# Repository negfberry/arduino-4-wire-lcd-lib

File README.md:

# arduino-4-wire-lcd-lib
Arduino 3 or 4 wire LCD library and hardware adapter.
Allows cheap 16x1, 16x2, 20x4 etc. LCDs to connect to an Arduino or similar using only 3 or 4 pins. Supports custom characters, and allows variable contrast (eight levels), and either backlight on/off (3 wire), or variable backlight (256 levels, 4 wire).

Includes library compatible with the Arduino LCD library.

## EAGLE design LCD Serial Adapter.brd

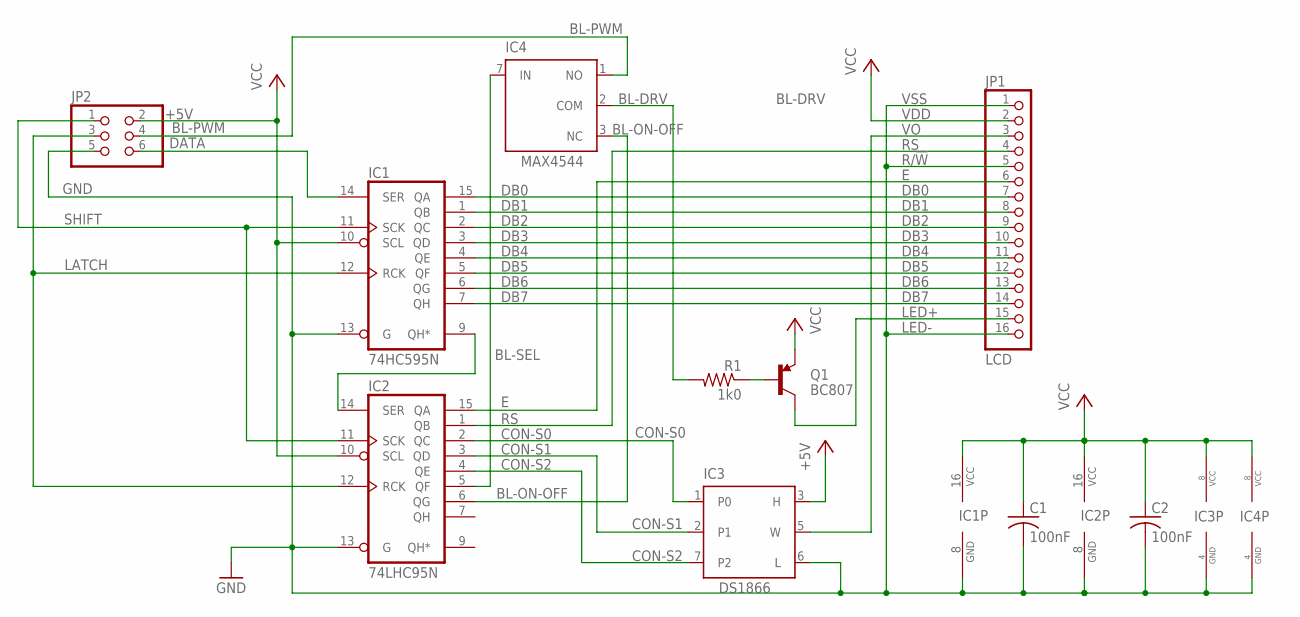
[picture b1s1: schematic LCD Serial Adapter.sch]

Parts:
C1, C2: 100nF; C0402
IC1: 74HC595N; SO16
IC2: 74LHC95N; SO16
IC3: DS1866Z; SOIC8
IC4: MAX4544; SOIC8
JP1: LCD; 1X16
JP2: PINHD-2X3; 2X03
Q1: BC807; SOT23-3
R1: 1k0; RES-VERT

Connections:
+5V: IC1.10 (SCL), IC2.10 (SCL), IC3.3 (H), JP1.2, JP2.2, Q1.2 (E)
BL-DRV: IC4.2 (COM), R1.2
BL-ON-OFF: IC2.6 (QG), IC4.3 (NC)
BL-PWM: IC4.1 (NO), JP2.4
BL-SEL: IC2.5 (QF), IC4.7 (IN)
CON-S0: IC2.2 (QC), IC3.1 (P0)
CON-S1: IC2.3 (QD), IC3.2 (P1)
CON-S2: IC2.4 (QE), IC3.7 (P2)
DATA: IC1.14 (SER), JP2.6
DB0: IC1.15 (QA), JP1.7
DB1: IC1.1 (QB), JP1.8
DB2: IC1.2 (QC), JP1.9
DB3: IC1.3 (QD), JP1.10
DB4: IC1.4 (QE), JP1.11
DB5: IC1.5 (QF), JP1.12
DB6: IC1.6 (QG), JP1.13
DB7: IC1.7 (QH), JP1.14
E: IC2.15 (QA), JP1.6
GND: C1.2, C2.2, IC1.8 (GND), IC1.13 (G), IC2.8 (GND), IC2.13 (G), IC3.4 (GND), IC3.6 (L), IC4.4 (GND), JP1.1, JP1.5, JP1.16, JP2.5
LATCH: IC1.12 (RCK), IC2.12 (RCK)
LED+: JP1.15, Q1.3 (C)
unnamed: IC1.9 (QH*), IC2.14 (SER)
unnamed: Q1.1 (B), R1.1
RS: IC2.1 (QB), JP1.4
SHIFT: IC1.11 (SCK), IC2.11 (SCK), JP2.1
VCC: C1.1, C2.1, IC1.16 (VCC), IC2.16 (VCC), IC3.8 (VCC), IC4.8 (VCC)
VO: IC3.5 (W), JP1.3

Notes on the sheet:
VSS
VDD
R/!W
LED-

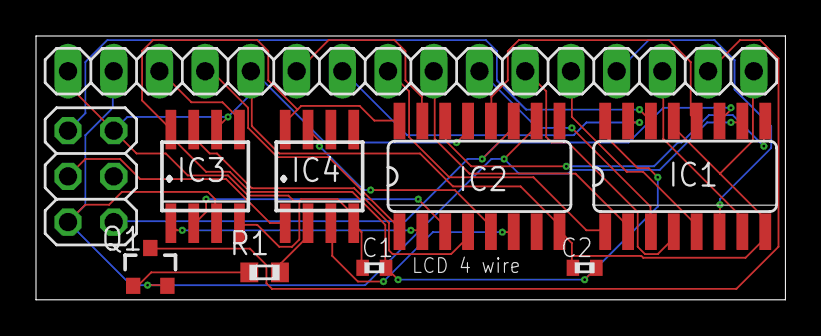
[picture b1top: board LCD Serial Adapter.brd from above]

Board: 2 copper layers, 41.6 x 14.7 mm, 10 parts (0 on the bottom side), 27 nets.

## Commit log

2016-08-17 Fix contrast signal names
